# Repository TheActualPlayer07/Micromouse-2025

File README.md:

# Micromouse 2025

Autonomous maze-solving robot built for the 2025 Micromouse competition. Custom PCB, Teensy 4.1, and a full online Flood Fill implementation with PID-based motion control.

---

## Hardware

- **Teensy 4.1** as the main controller
- **3× VL53L0X** Time-of-Flight sensors (front, left, right) — all on one I²C bus, assigned unique addresses at boot via XSHUT pins
- **BNO055 IMU** for absolute yaw (external crystal enabled)
- **2× DC motors** with quadrature encoders
- Custom PCB (KiCad files included)

---

## How it works

The robot uses an **online Flood Fill** algorithm. Before moving, it runs a BFS from the goal cells (the central 2×2 of the 16×16 maze) to assign every cell a distance value. At each step it reads the three sensors, updates the wall map, and if it finds a new wall it reruns the BFS before deciding where to go next. This way it always has an up-to-date shortest path even as the maze reveals itself.

Motion is handled by three PID loops running together each cycle:
- **Forward PID** — controls wheel speed via encoder feedback, with distance-based speed ramping (slows down as the front sensor reading drops)
- **Turning PID** — executes 90° and 180° turns using absolute yaw from the BNO055, with proper angle wraparound so it doesn't get confused near 0°/360°
- **Centering PID** — keeps the robot centered in the corridor by blending a correction term into the motor PWM outputs based on the difference between left and right sensor readings

---

## Files

```
main_control.ino         — setup/loop, wall detection, navigation decisions
floodfill.h/.cpp         — maze state, BFS, solve()
sensors.h/.cpp           — VL53L0X + BNO055 init and reads
motor_control.h/.cpp     — PWM, encoder ISRs, turn routines
forward_pid.h/.cpp       — speed PID
turning_pid.h/.cpp       — turn PID
centering_pid.h/.cpp     — wall centering PID
VL53L0X_SingleTest.ino   — standalone sensor test
micromouse2.kicad_sch    — schematic
micromouse2.kicad_pcb    — PCB layout
```

---

## Setup

Install [Teensyduino](https://www.pjrc.com/teensy/td_download.html), open `main_control.ino`, set board to Teensy 4.1, and install these libraries via the Library Manager:
- `VL53L0X` (Pololu)
- `Adafruit_BNO055` + `Adafruit_Sensor`

On boot the robot waits 5 seconds before starting — enough time to place it at the maze entrance and switch on motor power.

Key constants to tune for your physical setup are `WALL_THRESHOLD` (165 mm), `FRONT_WALL_THRESHOLD` (100 mm), and `TICKS_PER_MM` (7.38) in `floodfill.h`.

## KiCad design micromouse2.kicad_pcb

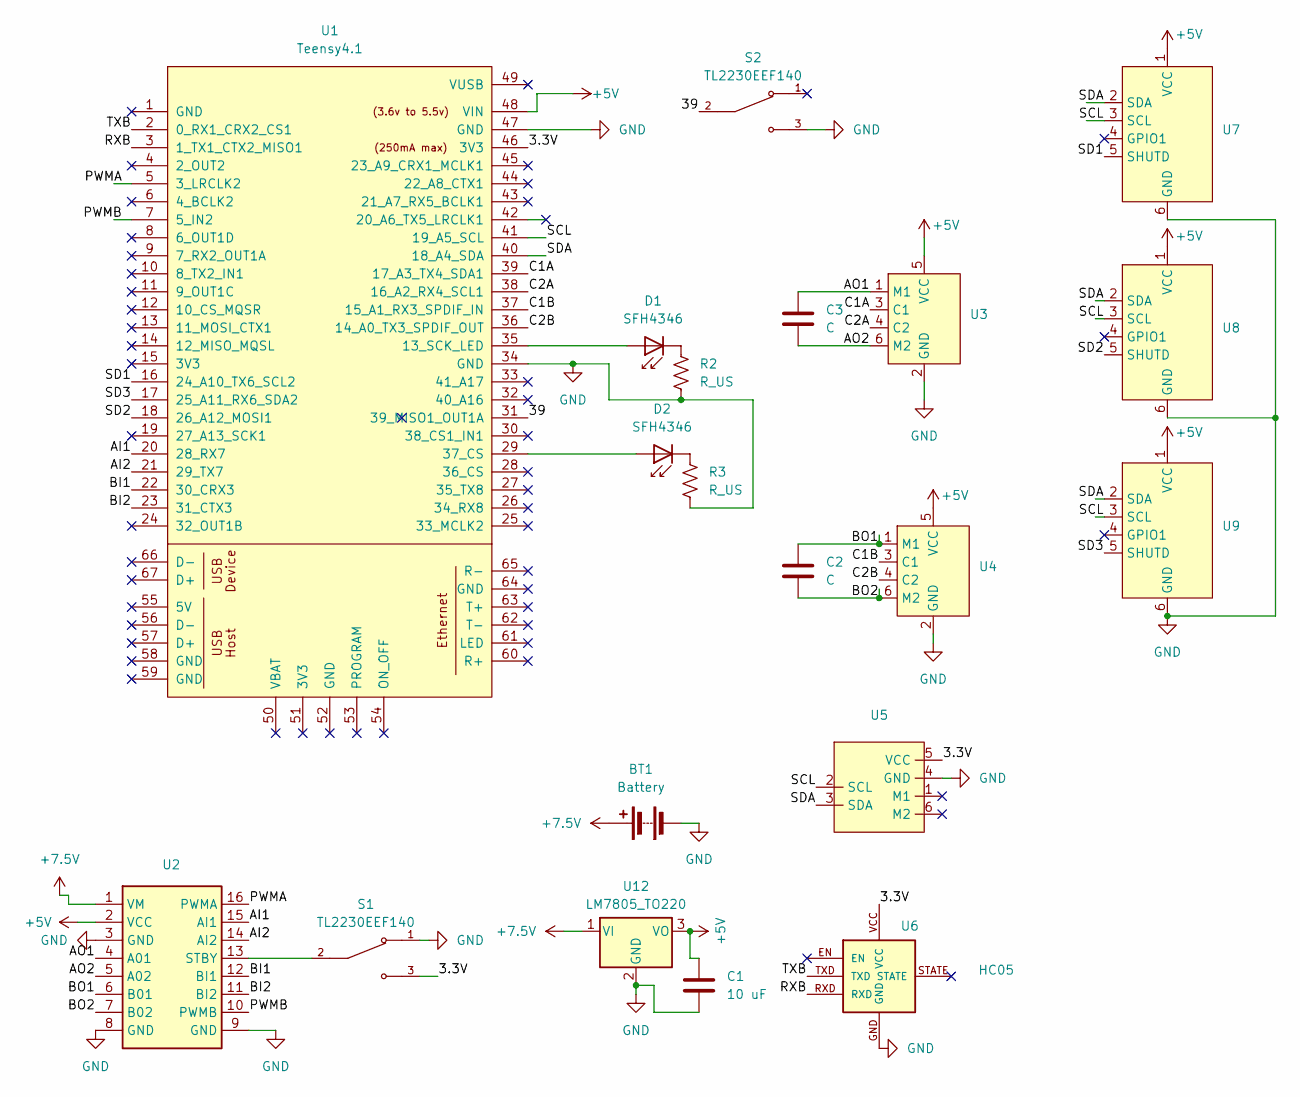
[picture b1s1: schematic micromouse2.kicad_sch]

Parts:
BT1: Battery; JST_VH_B2P-VH-B_1x02_P3.96mm_Vertical
C1: 10 uF; CP_Radial_D5.0mm_P2.00mm
C2, C3: C; C_Disc_D3.0mm_W1.6mm_P2.50mm
D1, D2: SFH4346; LED_D3.0mm_IRBlack
R2, R3: R_US; R_Axial_DIN0204_L3.6mm_D1.6mm_P5.08mm_Vertical
S1: TL2230EEF140; PinHeader_1x03_P1.27mm_Vertical; PARTREV E
S2: TL2230EEF140; SW_TL2230EEF140; PARTREV E
U1: Teensy4.1; Teensy41
U2: Motor_driver_tb6612fng
U3, U4: JST_XH_B6B-XH-A_1x06_P2.50mm_Vertical
U5, U7, U8, U9: PinHeader_1x06_P2.54mm_Vertical
U6: HC05
U12: LM7805_TO220; TO-220-3_Vertical

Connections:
+5V: C1.1, U1.48 (VIN), U2.2 (VCC), U3.5 (VCC), U4.5 (VCC), U7.1 (VCC), U8.1 (VCC), U9.1 (VCC), U12.3 (VO)
+7.5V: BT1.1 (+), U2.1 (VM), U12.1 (VI)
/3.3V: S1.3, U1.46 (3V3), U5.5 (VCC), U6.VCC
/39: S2.2, U1.31 (39_MISO1_OUT1A)
/AI1: U1.20 (28_RX7), U2.15 (AI1)
/AI2: U1.21 (29_TX7), U2.14 (AI2)
/AO1: C3.1, U2.4 (A01), U3.1 (M1)
/AO2: C3.2, U2.5 (A02), U3.6 (M2)
/BI1: U1.22 (30_CRX3), U2.12 (BI1)
/BI2: U1.23 (31_CTX3), U2.11 (BI2)
/BO1: C2.1, U2.6 (B01), U4.1 (M1)
/BO2: C2.2, U2.7 (B02), U4.6 (M2)
/C1A: U1.39 (17_A3_TX4_SDA1), U3.3 (C1)
/C1B: U1.37 (15_A1_RX3_SPDIF_IN), U4.3 (C1)
/C2A: U1.38 (16_A2_RX4_SCL1), U3.4 (C2)
/C2B: U1.36 (14_A0_TX3_SPDIF_OUT), U4.4 (C2)
/PWMA: U1.5 (3_LRCLK2), U2.16 (PWMA)
/PWMB: U1.7 (5_IN2), U2.10 (PWMB)
/RXB: U1.3 (1_TX1_CTX2_MISO1), U6.RXD
/SCL: U1.41 (19_A5_SCL), U5.2 (SCL), U7.3 (SCL), U8.3 (SCL), U9.3 (SCL)
/SD1: U1.16 (24_A10_TX6_SCL2), U7.5 (SHUTD)
/SD2: U1.18 (26_A12_MOSI1), U8.5 (SHUTD)
/SD3: U1.17 (25_A11_RX6_SDA2), U9.5 (SHUTD)
/SDA: U1.40 (18_A4_SDA), U5.3 (SDA), U7.2 (SDA), U8.2 (SDA), U9.2 (SDA)
/TXB: U1.2 (0_RX1_CRX2_CS1), U6.TXD
GND: BT1.2 (-), C1.2, R2.1, R3.1, S1.1, S2.3, U1.34 (GND), U1.47 (GND), U2.3 (GND), U2.8 (GND), U2.9 (GND), U3.2 (GND), U4.2 (GND), U5.4 (GND), U6.GND, U7.6 (GND), U8.6 (GND), U9.6 (GND), U12.2 (GND)
unnamed: D1.2 (A), U1.35 (13_SCK_LED)
unnamed: D1.1 (K), R2.2
unnamed: D2.2 (A), U1.29 (37_CS)
unnamed: D2.1 (K), R3.2
unnamed: S1.2, U2.13 (STBY)

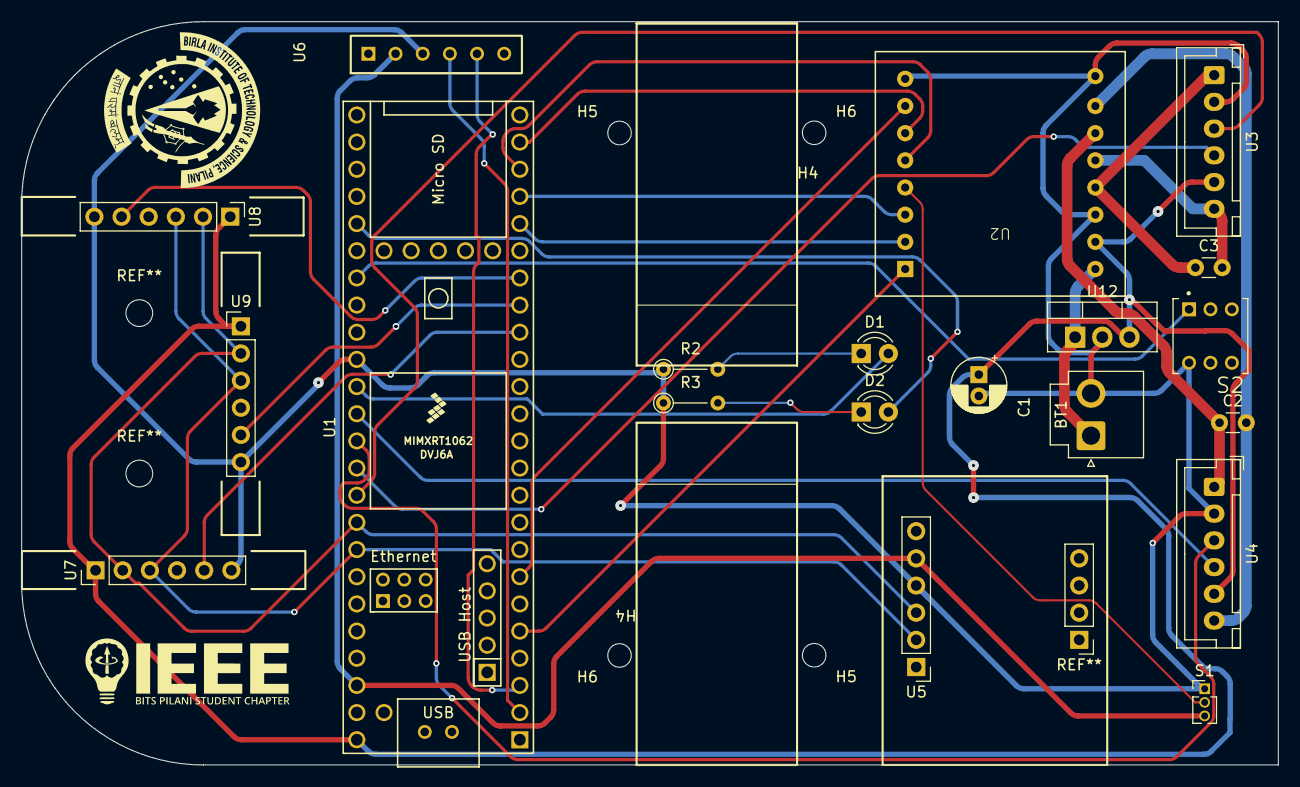
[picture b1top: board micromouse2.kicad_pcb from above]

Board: 2 copper layers, 117.5 x 69.5 mm, 24 parts (0 on the bottom side), 31 nets.

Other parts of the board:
H5, H5#2, H6, H6#2: MountingHole; MountingHole_2.2mm_M2

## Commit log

2026-01-16 Add micromouse control code
2026-01-22 made changes and added centering pid
2026-06-27 Add files via upload
    Uploaded final schematic and pcb design.
